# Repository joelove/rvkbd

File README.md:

# Raven Split Keyboard

The Raven keyboard (rvkbd) is a wireless, low-profile, split keyboard based on the [Corne keyboard](https://github.com/foostan/crkbd) by foostan. It has a 3x5 column staggered layout with 3 thumb keys and 1 extra outer pinky key.

The goal of this project is to create a split layout with an aggressive, irregular stagger to match a sub-integer [2D:4D ratio](https://en.wikipedia.org/wiki/Digit_ratio) of approximately 0.925. The 38-key layout is a product of countless iterations on [my personal keymap](images/example-keymap.png), aiming to minimize finger movement and total keystrokes whilst maintaining a clean, logical distinction between layers.

<h3 align="center" style="margin-top: 5rem">
  <a href="raven-split-38key/raven-split-38key__choc-hotswap-n!n/BUILD_GUIDE.md">
    🛠️ Version 1 Build Guide 🛠️
  </a>
</h3>

## Example Keymap

## Microcontrollers

The Raven is designed to be entirely wireless and built with the [nice!nano microcontroller](https://nicekeyboards.com/nice-nano/). A full list of international stockists is available on their website.

The keyboard is compatible with any wireless controller with a Pro Micro footprint. One of the best-received and easiest to obtain nice!nano clones is the [Supermini NRF5284](https://www.aliexpress.com/item/1005006035505133.html) which has been tested with this keyboard and works as expected.

> A comprehensive list of possible alternatives can be found [here](https://github.com/joric/nrfmicro/wiki/Alternatives). Most of these options are untested and you might run into unforeseen complexities when using an alternative microcontroller.

## Keycaps

The PCB key-spacing is designed for 17x17mm keycaps with a 2mm border radius. I've read that standard Kailh keycaps are 17x18mm so will probably not fit without modification.

The keyboard works best with Chosfox PBT keycaps which can be purchased from the [Mechanical Switch Store](https://www.aliexpress.com/item/1005004558099208.html) on AliExpress and shipped internationally. They also sell homing keys and 1.5U thumb keys [here](https://www.aliexpress.com/item/1005004780019538.html).

## Plate

Version 1 comes with [an edge-cuts gerber](raven-split-38key/raven-split-38key__choc-hotswap-n!n/pcb/gerber.zip  "download") intended to be cut from 1.2mm FR-4. Alternatively, an identical but untested DXF is included for lazer cutting other sheet materials.

> The plate should be exactly 1.2mm thick and fairly stiff to allow the low profile choc (v1) switches to attach easily and securely. The switches will slip out of a thicker plate more easily but the edges of the plate cuts are quite thin so the material needs to be very strong and not too brittle, e.g. carbon fibre or aluminum.

## Case

Version 1 is not intended to be used with a case and does not include a case model of any kind nor the required mounting holes. Instead, the board rests directly on the hotswap sockets and uses rubber feet for grip and stability. This is an intentional decision intended to reduce the height of the board but probably reduces the durability of the final product.

> If you want to use a case, I recommend adding several through-hole pads to the PCB file before having it fabricated. How you use those mounting holes and create the case itself is up to you. Common approaches include 3D-printing and making a layered case out of extra unprinted FR-4 or other lazer cut sheet materials.

## Firmware

The Raven uses [ZMK](https://zmk.dev/docs) for firmware. Because the PCB shares a wiring schematic with the Corne keyboard, it can be loaded with any existing 3x6 Corne configuration.

> Any repurposed Corne 3x6 keymap will be missing the outermost top and bottom keys due to the difference in physical layout. Any key mappings in these positions will not be accessible on the Raven.

If you want to customize the layout or create your own config, I have created a [custom shield and config repo](https://github.com/joelove/rvkbd-zmk-config). Just fork the repo and use the layout editor in the README to quickly and easily design your own.

> Flashable firmware artifacts can be found in the repo _Actions_ tab, just download them then hit the reset key twice on each half and drag each firmware file onto the "NICENANO" drive that appears.

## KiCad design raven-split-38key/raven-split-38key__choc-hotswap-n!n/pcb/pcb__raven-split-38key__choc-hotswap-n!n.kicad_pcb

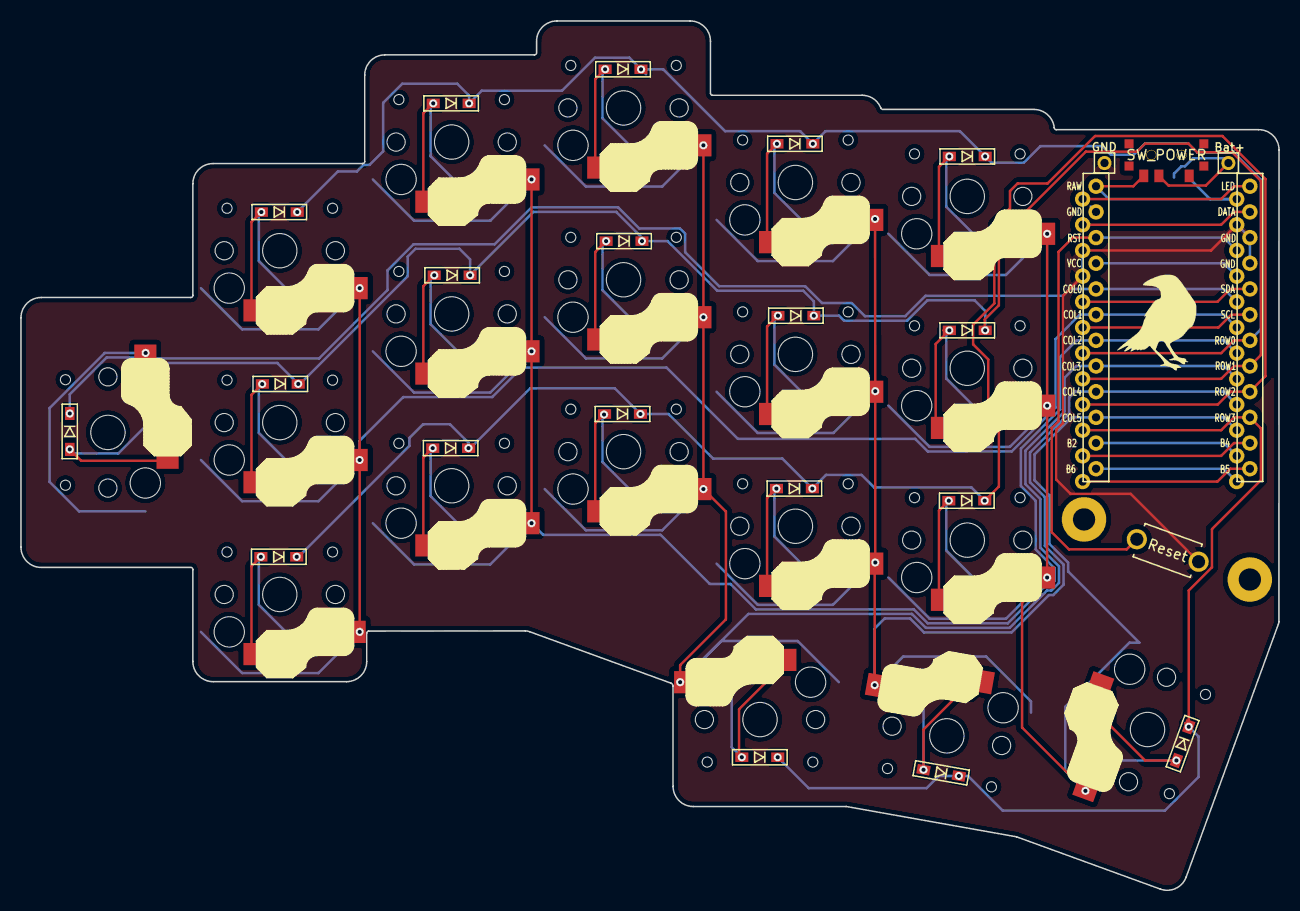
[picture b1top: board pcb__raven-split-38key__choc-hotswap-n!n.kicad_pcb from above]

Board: 2 copper layers, 124.4 x 86.0 mm, 46 parts (1 on the bottom side), 33 nets.

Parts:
Bat+: MountingHole_Pad; 1pin_conn
D2, D3, D4, D5, D6, D7, D8, D9, D10, D11, D12, D14, D15, D16, D17, D18, D19, D20, D21: D; D3_SMD
GND: MountingHole_Pad; 1pin_conn
M2_0, M2_1: MountingHole_2.2mm_M2_Pad
RSW1: Reset; ResetSW
SW2, SW3, SW4, SW5, SW6, SW7, SW8, SW9, SW10, SW11, SW12, SW14, SW15, SW16, SW17, SW18, SW19, SW20: SW_PUSH; Choc_Hotswap
SW21: SW_PUSH; Choc_Hotswap_1.5u
SW_POWER: SW_SPDT; SPDT_C128955
SW_POWER#2: SW_SPDT; SPDT_C128955
U1: ProMicro; ProMicro_v2

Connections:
Bat+: Bat+.1, SW_POWER.2, SW_POWER#2.2
GND: GND.1, RSW1.2, U1.3, U1.4, U1.23
unnamed: D2.2, SW2.2
unnamed: D3.2, SW3.2
unnamed: D4.2, SW4.2
unnamed: D5.2, SW5.2
unnamed: D6.2, SW6.2
unnamed: D7.2, SW7.2
unnamed: D8.2, SW8.2
unnamed: D9.2, SW9.2
unnamed: D10.2, SW10.2
unnamed: D11.2, SW11.2
unnamed: D12.2, SW12.2
unnamed: D14.2, SW14.2
unnamed: D15.2, SW15.2
unnamed: D16.2, SW16.2
unnamed: D17.2, SW17.2
unnamed: D18.2, SW18.2
unnamed: D19.2, SW19.2
unnamed: D20.2, SW20.2
unnamed: D21.2, SW21.2
unnamed: SW_POWER.3, SW_POWER#2.3, U1.24
col0: SW7.1, U1.20
col1: SW2.1, SW8.1, SW14.1, U1.19
col2: SW3.1, SW9.1, SW15.1, U1.18
col3: SW4.1, SW10.1, SW16.1, SW19.1, U1.17
col4: SW5.1, SW11.1, SW17.1, SW20.1, U1.16
col5: SW6.1, SW12.1, SW18.1, SW21.1, U1.15
reset: RSW1.1, U1.22
row0: D2.1, D3.1, D4.1, D5.1, D6.1, U1.7
row1: D7.1, D8.1, D9.1, D10.1, D11.1, D12.1, U1.8
row2: D14.1, D15.1, D16.1, D17.1, D18.1, U1.9
row3: D19.1, D20.1, D21.1, U1.10

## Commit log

2023-10-22 add README and initial KiCAD files
2023-10-23 generate gerbers, update README and test
2024-04-19 update example keymap
2024-07-05 add plate
2024-07-27 add components to README, add plate, and update all gerbers
2024-07-28 add photo of built keyboard
2024-07-28 remove tools section for now
2024-07-28 extract v1 build guide
2024-09-11 add firmware info to the readme
2024-09-11 add image to build guide
2025-03-10 add wiring diagram
2025-03-10 update wiring diagram to be double sided
2025-03-10 update keymap
2025-03-10 add sponsor icon
2025-03-10 add sponsor badge
